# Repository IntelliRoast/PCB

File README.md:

View this project on [CADLAB.io](https://cadlab.io/project/1622). 

# PCB

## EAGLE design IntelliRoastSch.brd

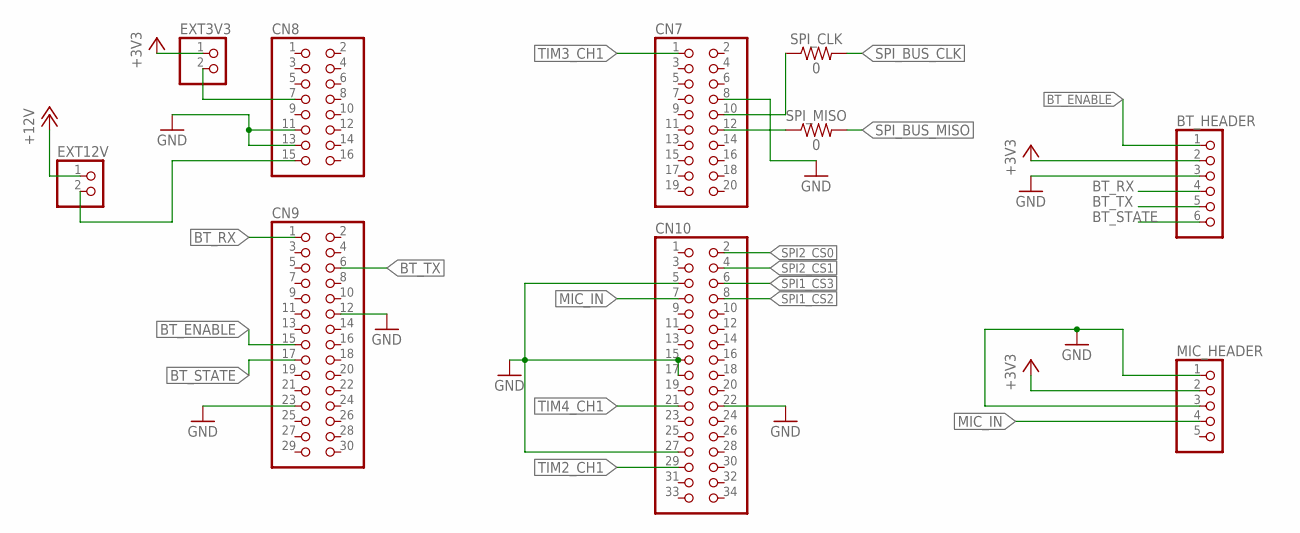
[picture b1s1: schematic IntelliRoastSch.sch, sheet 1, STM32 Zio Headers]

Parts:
BT_HEADER: HC-05-BREAKOUT; HC-O5_HEADER
CN7: PINHD-2X10; 2X10
CN8: PINHD-2X8; 2X08
CN9: PINHD-2X15; 2X15
CN10: PINHD-2X17; 2X17
EXT3V3, EXT12V: PINHD-1X2; 1X02
MIC_HEADER: PINHD-1X5; 1X05
SPI_CLK: 0; 0603
SPI_MISO: 0; 0603

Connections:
+3V3: BT_HEADER.2, EXT3V3.1, MIC_HEADER.2; also elsewhere on the board
+12V: EXT12V.1; also elsewhere on the board
BT_ENABLE: BT_HEADER.1, CN9.15
BT_RX: BT_HEADER.4, CN9.1
BT_STATE: BT_HEADER.6, CN9.17
BT_TX: BT_HEADER.5, CN9.6
GND: BT_HEADER.3, CN7.8, CN8.11, CN8.13, CN9.12, CN9.23, CN10.5, CN10.15, CN10.17, CN10.22, CN10.27, MIC_HEADER.1, MIC_HEADER.3; also elsewhere on the board
MIC_IN: CN10.7, MIC_HEADER.4
unnamed: CN8.7, EXT3V3.2
unnamed: CN8.15, EXT12V.2
SPI1_CS2: CN10.8; also elsewhere on the board
SPI1_CS3: CN10.6; also elsewhere on the board
SPI1_MISO: CN7.12, SPI_MISO.1
SPI1_SCK: CN7.10, SPI_CLK.1
SPI2_CS0: CN10.2; also elsewhere on the board
SPI2_CS1: CN10.4; also elsewhere on the board
SPI_BUS_CLK: SPI_CLK.2; also elsewhere on the board
SPI_BUS_MISO: SPI_MISO.2; also elsewhere on the board
TIM2_CH1: CN10.29
TIM3_CH1: CN7.1; also elsewhere on the board
TIM4_CH1: CN10.21

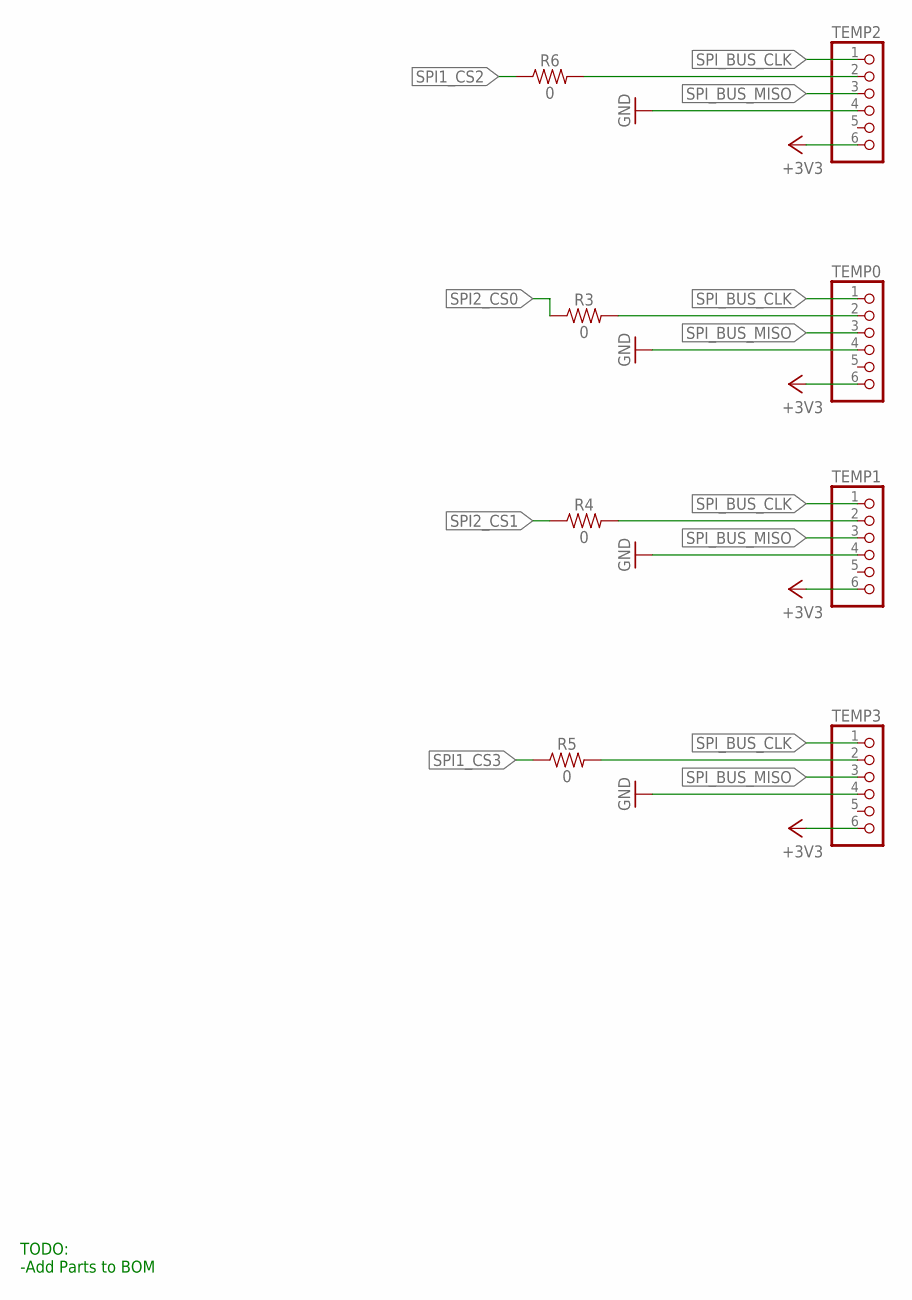
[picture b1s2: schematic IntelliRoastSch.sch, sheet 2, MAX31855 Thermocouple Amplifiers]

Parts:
R3, R4, R5, R6: 0; 0603
TEMP0, TEMP1, TEMP2, TEMP3: ADAFRUIT-MAX31855-BREAKOUT; MAX31855_HEADER

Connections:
+3V3: TEMP0.6, TEMP1.6, TEMP2.6, TEMP3.6; also elsewhere on the board
GND: TEMP0.4, TEMP1.4, TEMP2.4, TEMP3.4; also elsewhere on the board
SPI1_CS2: R6.1; also elsewhere on the board
SPI1_CS2_RES: R6.2, TEMP2.2
SPI1_CS3: R5.1; also elsewhere on the board
SPI1_CS3_RES: R5.2, TEMP3.2
SPI2_CS0: R3.1; also elsewhere on the board
SPI2_CS0_RES: R3.2, TEMP0.2
SPI2_CS1: R4.1; also elsewhere on the board
SPI2_CS1_RES: R4.2, TEMP1.2
SPI_BUS_CLK: TEMP0.1, TEMP1.1, TEMP2.1, TEMP3.1; also elsewhere on the board
SPI_BUS_MISO: TEMP0.3, TEMP1.3, TEMP2.3, TEMP3.3; also elsewhere on the board

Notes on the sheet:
TODO: -Add Parts to BOM

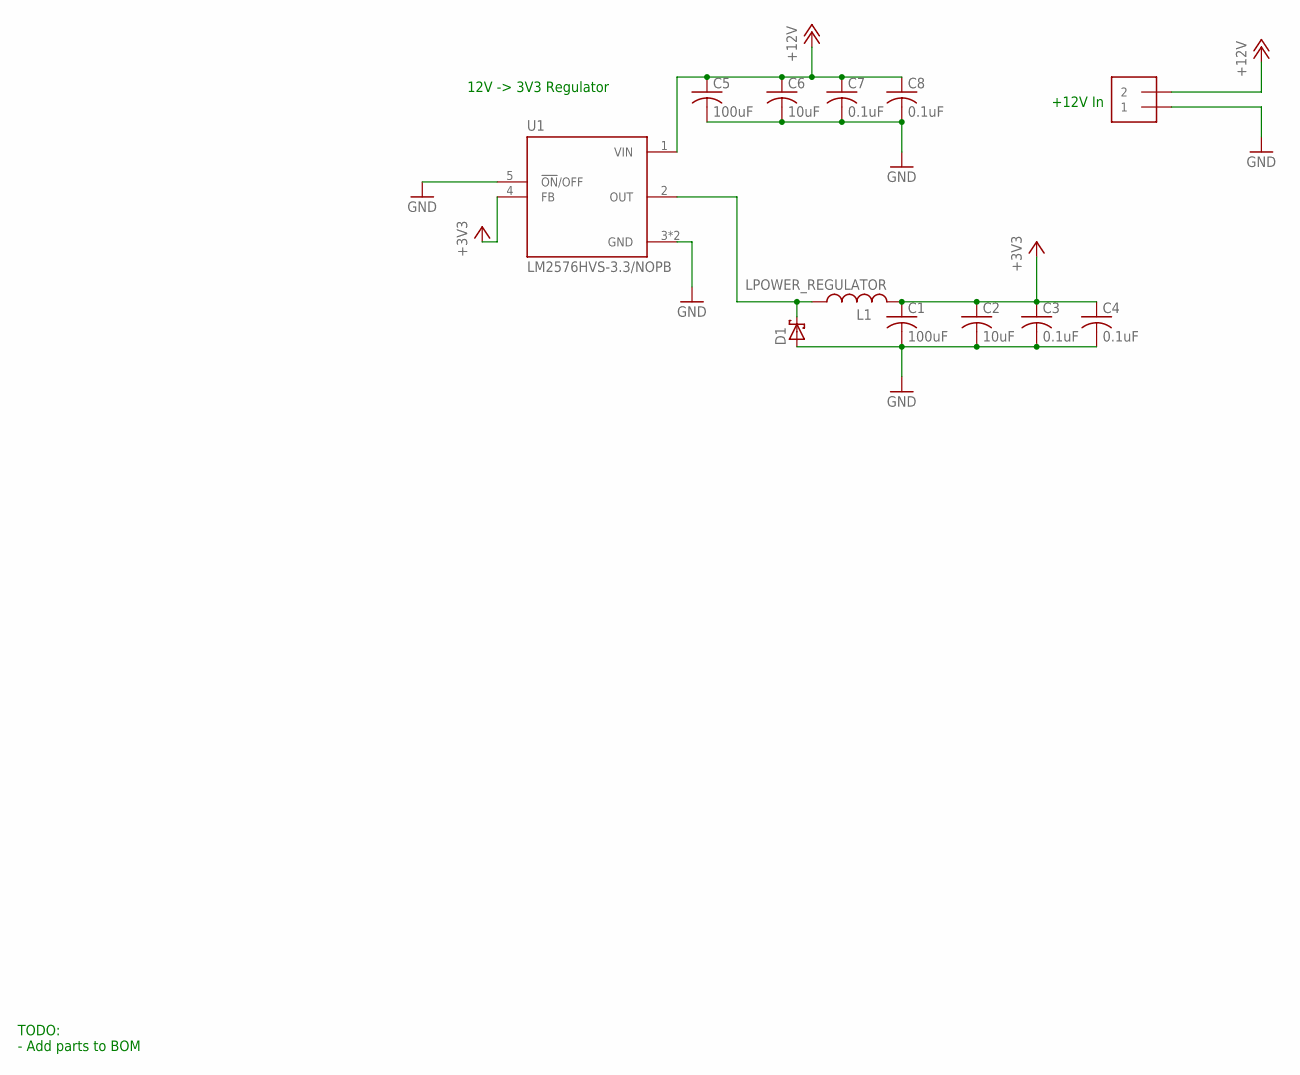
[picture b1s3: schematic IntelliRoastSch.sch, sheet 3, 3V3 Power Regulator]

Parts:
C1, C5: 100uF; C1210
C2, C6: 10uF; C0805
C3, C4, C7, C8: 0.1uF; C0603
D1: SCHOTTKY-DIODESMC; DIODE_SMC
L1: LPOWER_REGULATOR; L74477020
PWR_IN: 1X2-3.5MM
U1: LM2576HVS-3.3/NOPB; TO170P1435X465-6N

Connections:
+3V3: C1.1, C2.1, C3.1, C4.1, L1.2, U1.4 (FB); also elsewhere on the board
+12V: C5.1, C6.1, C7.1, C8.1, PWR_IN.2, U1.1 (VIN); also elsewhere on the board
GND: C1.2, C2.2, C3.2, C4.2, C5.2, C6.2, C7.2, C8.2, D1.A (C), PWR_IN.1, U1.3 (GND), U1.5 (!ON!/OFF), U1.6 (GND); also elsewhere on the board
OUT: D1.C (A), L1.1, U1.2 (OUT)

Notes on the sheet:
TODO: - Add parts to BOM
+12V In
12V -> 3V3 Regulator

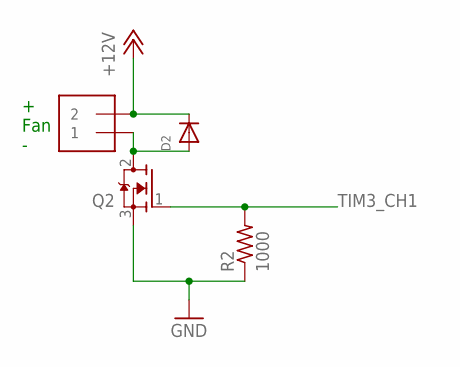
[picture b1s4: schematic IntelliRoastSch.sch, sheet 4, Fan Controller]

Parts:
D2: DIODESMA; SMADIODE
FAN: 1X2-3.5MM
Q2: MOSFET-NGDS_TO220V; TO220V
R2: 1000; R0603

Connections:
+12V: D2.C, FAN.2; also elsewhere on the board
FAN_TO_MOS: D2.A, FAN.1, Q2.2 (D)
GND: Q2.3 (S), R2.1; also elsewhere on the board
TIM3_CH1: Q2.1 (G), R2.2; also elsewhere on the board

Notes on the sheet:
+ Fan -

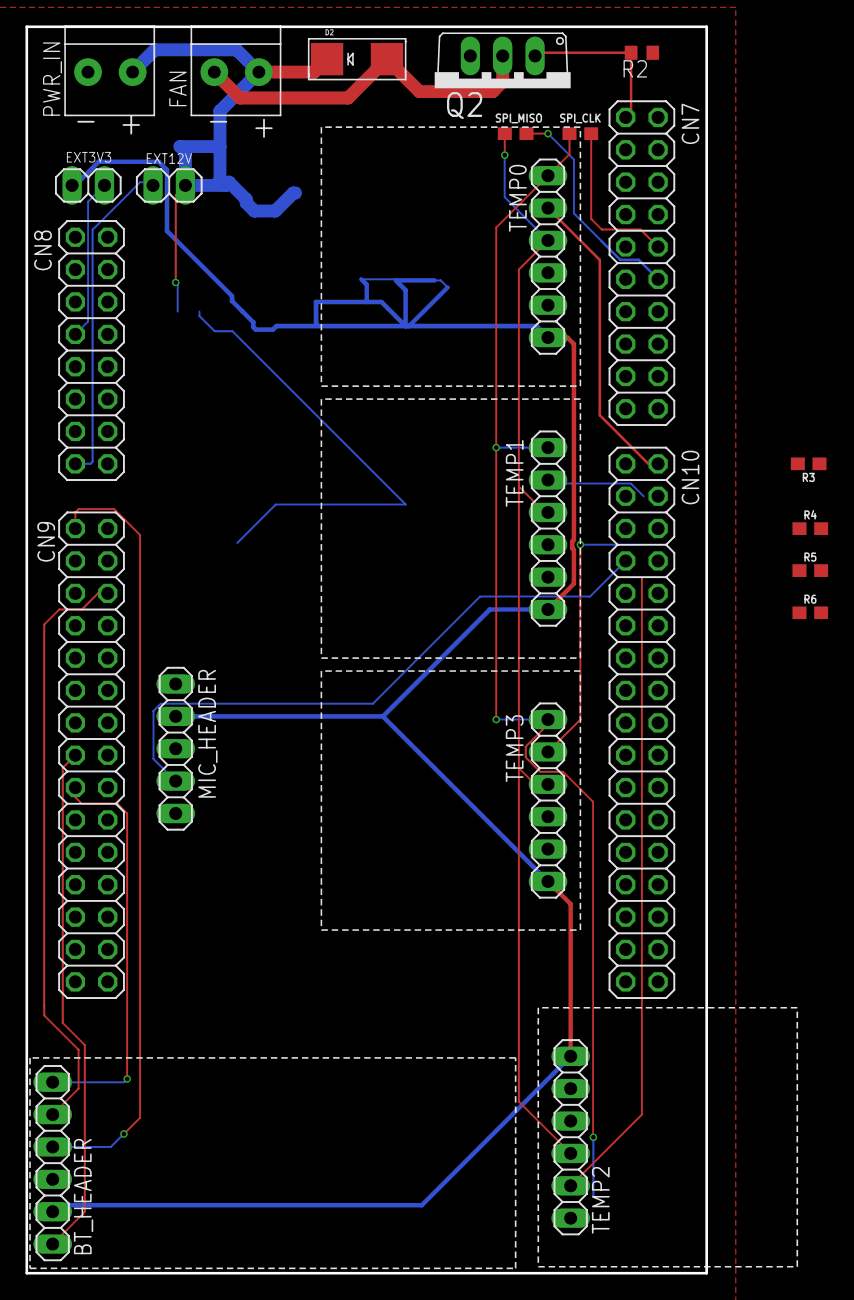
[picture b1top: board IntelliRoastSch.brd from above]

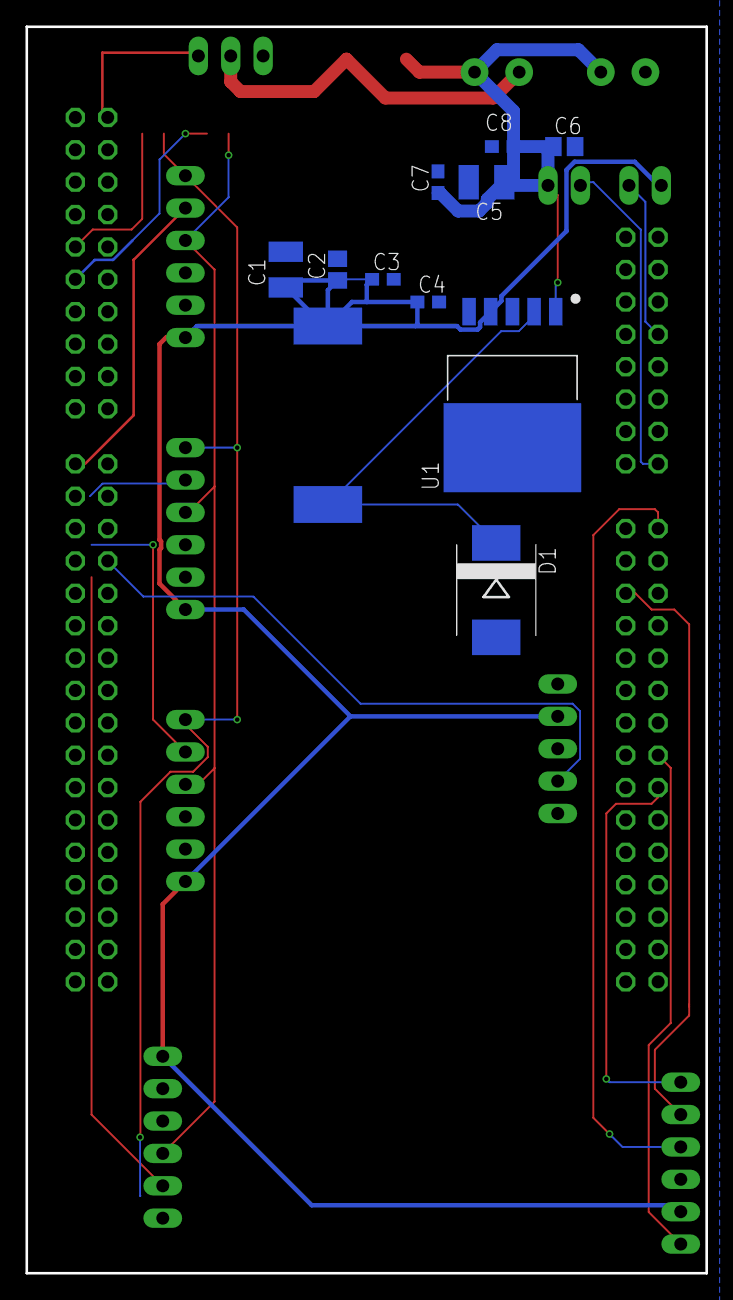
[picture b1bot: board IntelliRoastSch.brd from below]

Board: 2 copper layers, 53.3 x 97.8 mm, 34 parts (11 on the bottom side), 25 nets.

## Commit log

2019-01-10 with stmicro microprocessor
2019-01-11 Added copies of MAX31855
2019-01-17 Added MAX3221 chip
2019-01-22 Updated with pin labels
2019-01-23 Added zero Ohm resistors to RX and TX lines incase we're dumb and got it backwards
2019-02-25 updated pins
2019-02-25 updated with headers
2019-02-25 moved componenets into separate pages for each subsystem
2019-02-26 Added page for 3v3 Power Regulator
2019-02-27 fan driver added
2019-02-27 Merged changes to have both power regulation and fan controller
2019-02-27 Moved Fan controller to separate page, reworked it a bit, and Added todo's to some pages
2019-02-27 Added Bluetooth Header
2019-02-27 Should click save before commiting changes
2019-02-27 added headers for thermocouples.
2019-02-27 Added header for Microphone
2019-02-28 un-used nets deleted
2019-02-28 Started working on Board
2019-03-01 added power and ground connections to F207 Headers, connected BT pins to F207 Headers, Added jumpers to configure power delivery to F207
2019-03-01 Arranged the components on board, need to add gnd, 3v3, 12v, and gnd planes and then start to route board
2019-03-01 Routed Board and added GND Planes to top and bottom
2019-03-02 Revert "un-used nets deleted"
    This reverts commit ec7ee393598e0a413738f2441cf304c66971c427.
2019-03-02 Replaced Mosfet Footprint with virtical instead of horizontal
2019-03-02 removed unneeded files
2019-03-02 added a gitignore file
2019-03-03 Backlink to CADLAB.io has been added.
2019-03-04 Moved Mic Header and tried to straighten up some of the traces. Don't think I actually helped anything.
2019-03-11 Redid the board. Should have better tolorences and the traces are better laid out. Need to add 0Ω resistors on all the connections if we need to change things around.
2019-03-19 added zero ohms

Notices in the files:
parts and their libraries:
SparkFun-Resistors: Licensing: Creative Commons ShareAlike 4.0 International - https://creativecommons.org/licenses/by-sa/4.0
